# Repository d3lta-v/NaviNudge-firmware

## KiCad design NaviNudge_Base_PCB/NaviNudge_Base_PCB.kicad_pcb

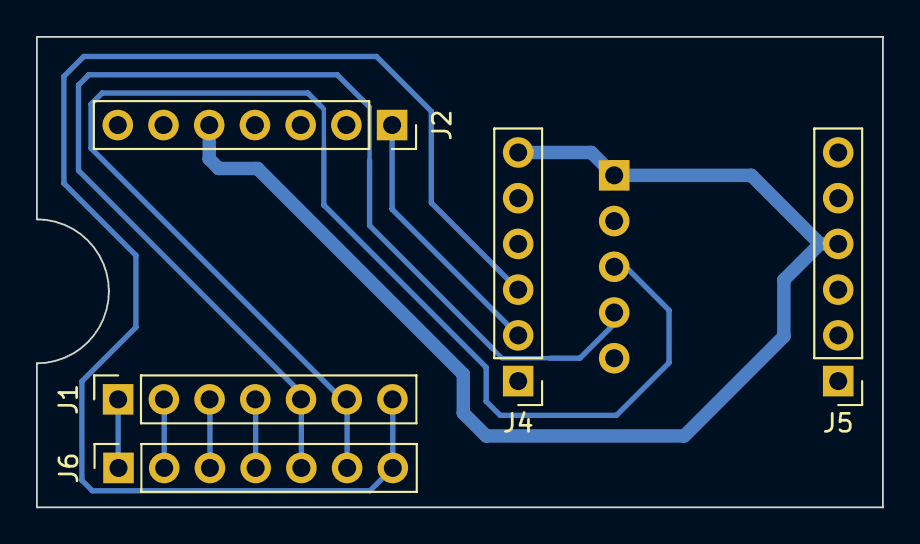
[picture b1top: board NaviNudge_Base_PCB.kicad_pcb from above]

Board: 2 copper layers, 47.0 x 26.1 mm, 6 parts (1 on the bottom side), 10 nets.

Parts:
J1: Xiao_Left; PinSocket_1x07_P2.54mm_Vertical
J2: Xiao_Right; PinSocket_1x07_P2.54mm_Vertical
J3: DRV2605_underboard; PinHeader_1x05_P2.54mm_Vertical
J4: BNO085_Bottom; PinHeader_1x06_P2.54mm_Vertical
J5: BNO085_Top; PinHeader_1x06_P2.54mm_Vertical
J6: Xiao_Left_Headers; PinSocket_1x07_P2.54mm_Vertical

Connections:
+3V3: J2.5, J3.1, J4.6, J5.4
/D0: J1.1, J6.1
/D1: J1.2, J6.2
/D2: J1.3, J6.3
/D3: J1.4, J6.4
/D4_SDA: J1.5, J3.4, J6.5
/D5_SCL: J1.6, J3.3, J6.6
/D6_TX: J1.7, J4.3, J6.7
/D7_RX: J2.1, J4.2
GND: J2.6, J3.2, J4.4

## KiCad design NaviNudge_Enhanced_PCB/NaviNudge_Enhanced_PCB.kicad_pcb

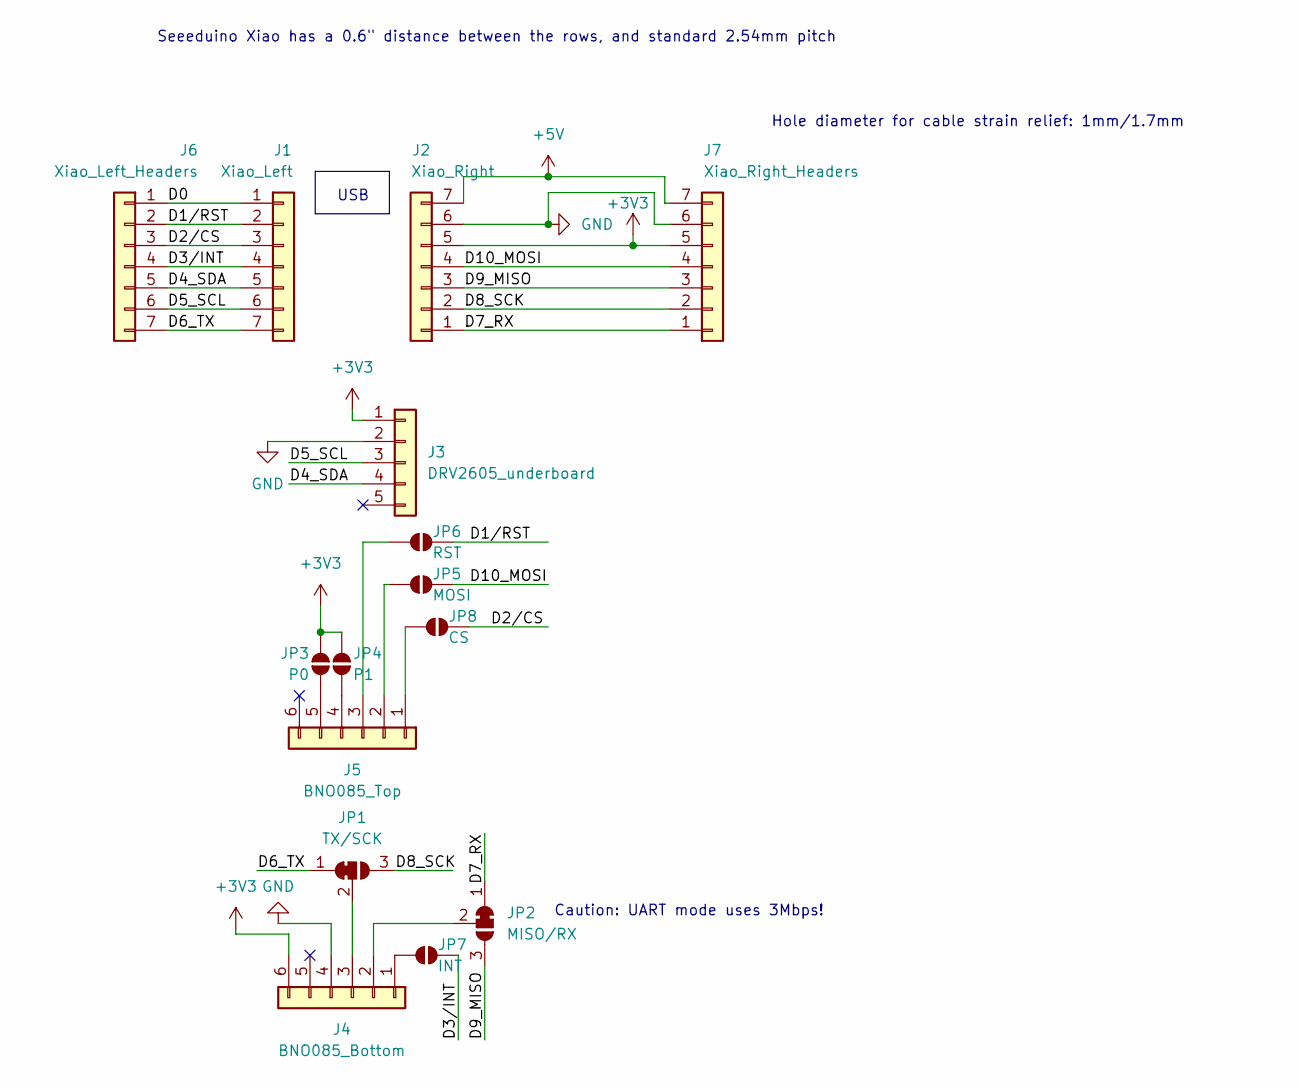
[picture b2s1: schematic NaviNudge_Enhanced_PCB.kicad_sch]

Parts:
J1: Xiao_Left; PinSocket_1x07_P2.54mm_Vertical
J2: Xiao_Right; PinSocket_1x07_P2.54mm_Vertical
J3: DRV2605_underboard; PinHeader_1x05_P2.54mm_Vertical
J4: BNO085_Bottom; PinHeader_1x06_P2.54mm_Vertical
J5: BNO085_Top; PinHeader_1x06_P2.54mm_Vertical
J6: Xiao_Left_Headers; PinSocket_1x07_P2.54mm_Vertical
J7: Xiao_Right_Headers; PinSocket_1x07_P2.54mm_Vertical
JP1: TX/SCK; SolderJumper-3_P1.3mm_Bridged12_Pad1.0x1.5mm
JP2: MISO/RX; SolderJumper-3_P1.3mm_Bridged12_Pad1.0x1.5mm
JP3: P0; SolderJumper-2_P1.3mm_Open_Pad1.0x1.5mm
JP4: P1; SolderJumper-2_P1.3mm_Open_Pad1.0x1.5mm
JP5: MOSI; SolderJumper-2_P1.3mm_Open_Pad1.0x1.5mm
JP6: RST; SolderJumper-2_P1.3mm_Open_Pad1.0x1.5mm
JP7: INT; SolderJumper-2_P1.3mm_Open_Pad1.0x1.5mm
JP8: CS; SolderJumper-2_P1.3mm_Open_Pad1.0x1.5mm

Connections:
+3V3: J2.5, J3.1, J4.6, J7.5, JP3.1 (A), JP4.1 (A)
+5V: J2.7, J7.7
/D0: J1.1, J6.1
/D1/RST: J1.2, J6.2, JP6.2 (B)
/D2/CS: J1.3, J6.3, JP8.2 (B)
/D3/INT: J1.4, J6.4, JP7.2 (B)
/D4_SDA: J1.5, J3.4, J6.5
/D5_SCL: J1.6, J3.3, J6.6
/D6_TX: J1.7, J6.7, JP1.1 (A)
/D7_RX: J2.1, J7.1, JP2.1 (A)
/D8_SCK: J2.2, J7.2, JP1.3 (B)
/D9_MISO: J2.3, J7.3, JP2.3 (B)
/D10_MOSI: J2.4, J7.4, JP5.2 (B)
GND: J2.6, J3.2, J4.4, J7.6
unnamed: J4.1, JP7.1 (A)
unnamed: J4.2, JP2.2 (C)
unnamed: J4.3, JP1.2 (C)
unnamed: J5.1, JP8.1 (A)
unnamed: J5.2, JP5.1 (A)
unnamed: J5.3, JP6.1 (A)
unnamed: J5.4, JP4.2 (B)
unnamed: J5.5, JP3.2 (B)

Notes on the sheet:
USB
Seeeduino Xiao has a 0.6" distance between the rows, and standard 2.54mm pitch
Hole diameter for cable strain relief: 1mm/1.7mm
Caution: UART mode uses 3Mbps!

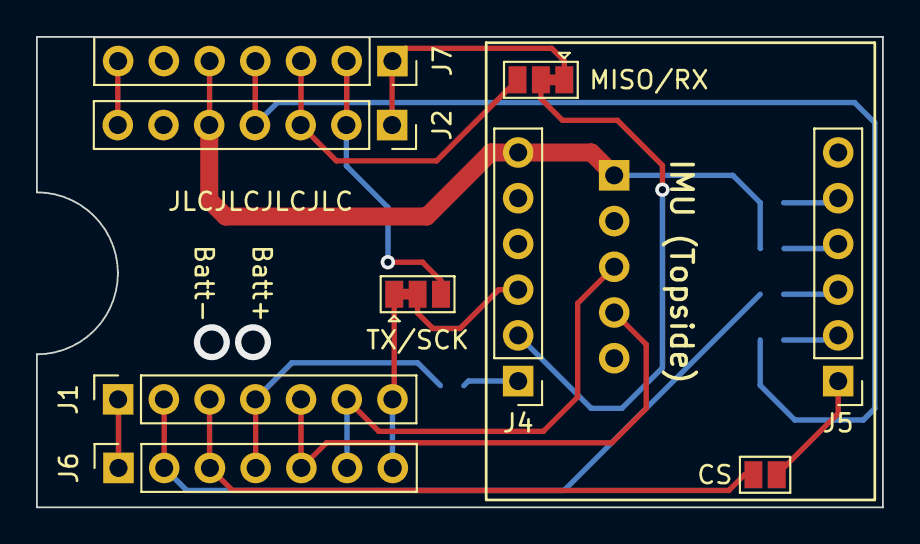
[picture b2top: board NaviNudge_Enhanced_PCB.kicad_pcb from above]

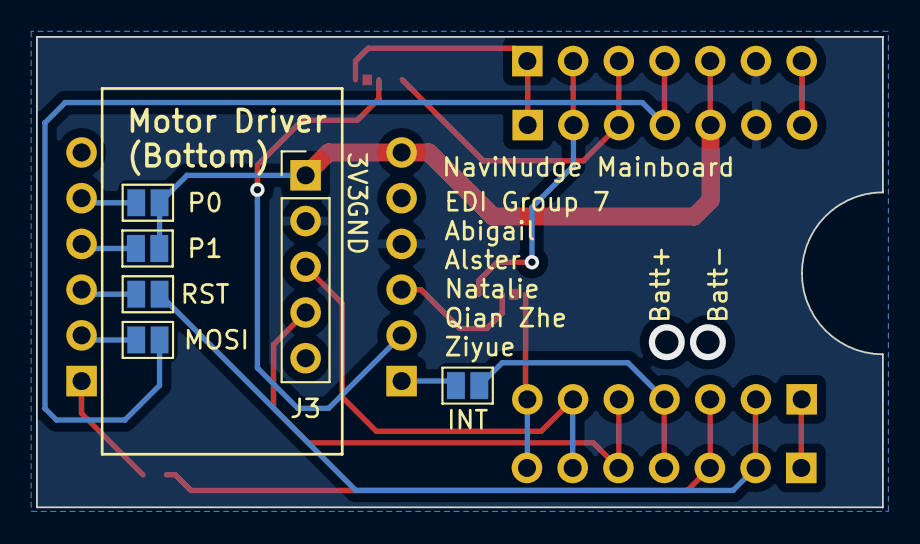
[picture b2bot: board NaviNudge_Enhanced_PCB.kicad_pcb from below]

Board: 2 copper layers, 47.0 x 26.1 mm, 15 parts (6 on the bottom side), 22 nets.

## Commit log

2024-07-30 added PCBs
2024-07-30 added more testing related code
2024-07-30 added basic bluetooth server functionality
2024-07-31 transitioned to platformio, basic bluetooth functionality complete
2024-07-31 added code for walking guidance IMU data transmit, and mode setting via phone using another characteristic
2024-08-03 fixed issue with module not transitioning to low power
2024-08-06 reduced cpu clock speed to save power
2024-08-06 added status LEDs
2024-08-06 added bearing write capability
2024-08-06 added haptics (finally!)
